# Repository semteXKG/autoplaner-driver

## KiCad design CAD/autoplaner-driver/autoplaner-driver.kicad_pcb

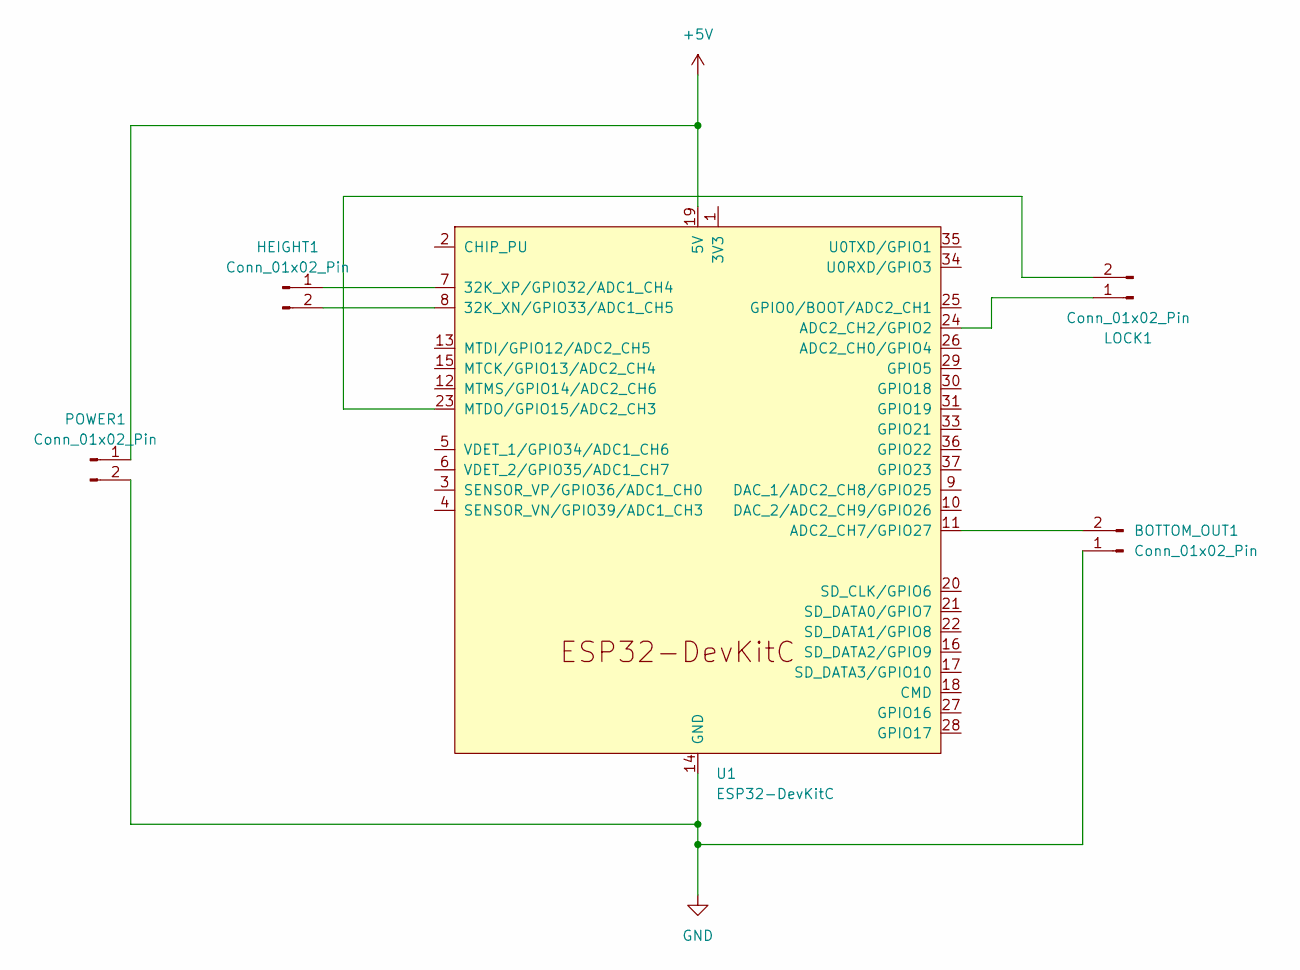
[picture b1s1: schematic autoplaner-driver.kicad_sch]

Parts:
BOTTOM_OUT1: Conn_01x02_Pin; JST_XH_B2B-XH-A_1x02_P2.50mm_Vertical
HEIGHT1: Conn_01x02_Pin; JST_XH_B2B-XH-A_1x02_P2.50mm_Vertical
LOCK1: Conn_01x02_Pin; JST_XH_B2B-XH-A_1x02_P2.50mm_Vertical
POWER1: Conn_01x02_Pin; JST_XH_B2B-XH-A_1x02_P2.50mm_Vertical
U1: ESP32-DevKitC

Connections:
+5V: POWER1.1, U1.19 (5V)
GND: BOTTOM_OUT1.1, POWER1.2, U1.14 (GND), U1.32 (GND), U1.38 (GND)
unnamed: BOTTOM_OUT1.2, U1.11 (ADC2_CH7/GPIO27)
unnamed: HEIGHT1.1, U1.7 (32K_XP/GPIO32/ADC1_CH4)
unnamed: HEIGHT1.2, U1.8 (32K_XN/GPIO33/ADC1_CH5)
unnamed: LOCK1.1, U1.24 (ADC2_CH2/GPIO2)
unnamed: LOCK1.2, U1.23 (MTDO/GPIO15/ADC2_CH3)

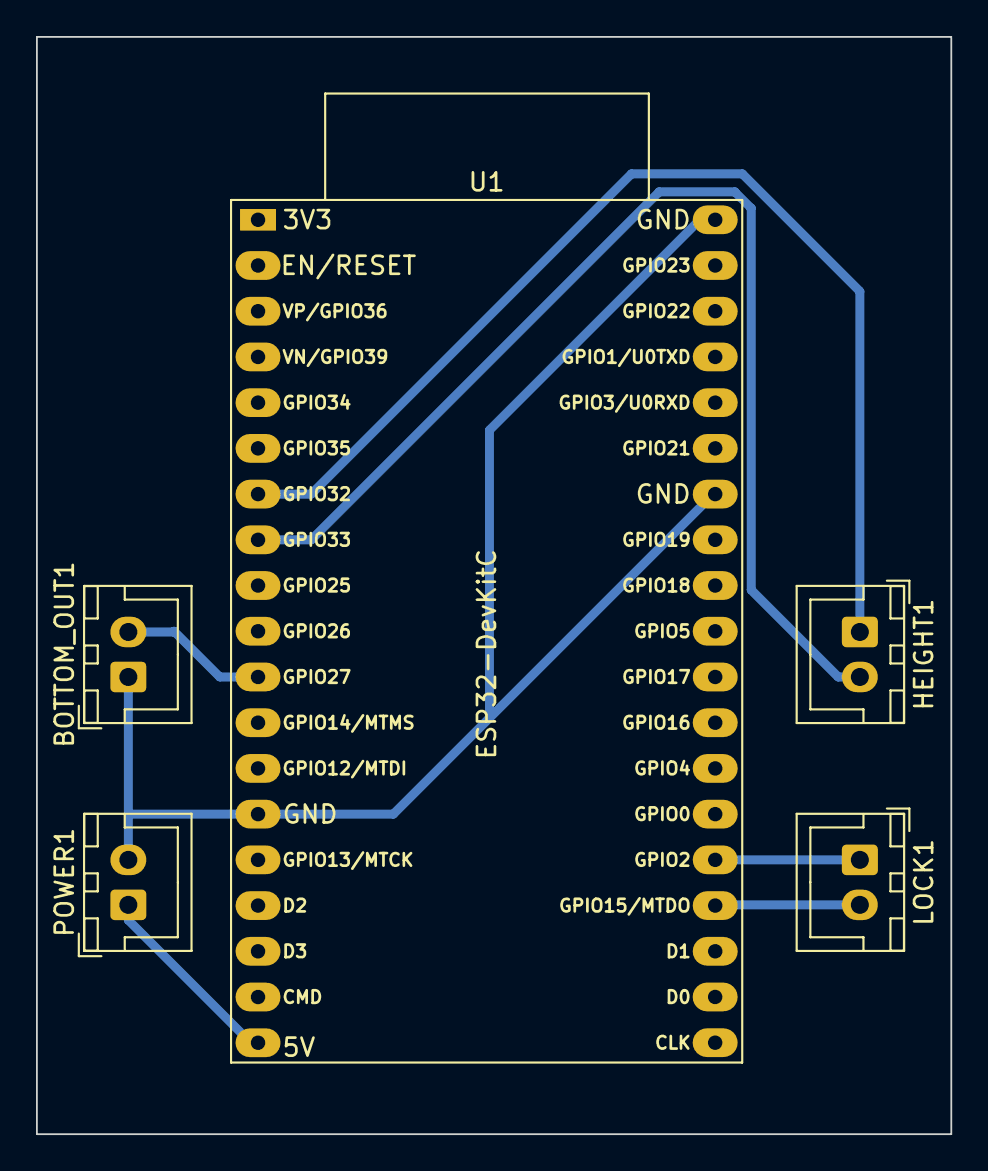
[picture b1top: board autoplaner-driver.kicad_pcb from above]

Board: 2 copper layers, 50.8 x 61.0 mm, 5 parts (0 on the bottom side), 7 nets.

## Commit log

2024-01-04 synced source with controller
2024-01-04 Separated monolith
2024-01-04 smaller upgrades to handshake
2024-01-05 Changed MemModel to Dynamic Allocation
2024-01-05 fixing sensors
2024-01-05 NVstuff is now all handled on driver
2024-01-06 fixing logging output
2024-01-06 Removing logspam
2024-01-20 adding kicad
